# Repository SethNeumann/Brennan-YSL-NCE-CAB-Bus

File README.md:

# REPO NAME: Brennan-YSL-NCE-CAB-Bus
## License: Creative Commons Attribution-NonCommercial-ShareAlike

NCE Cab Bus Distribution board for the Yosemite Short Line Modular group, by Richard Brennan
- 4 RJ45 Jacks
- Optional power injection via 2.1mm barrel connector
- power LED

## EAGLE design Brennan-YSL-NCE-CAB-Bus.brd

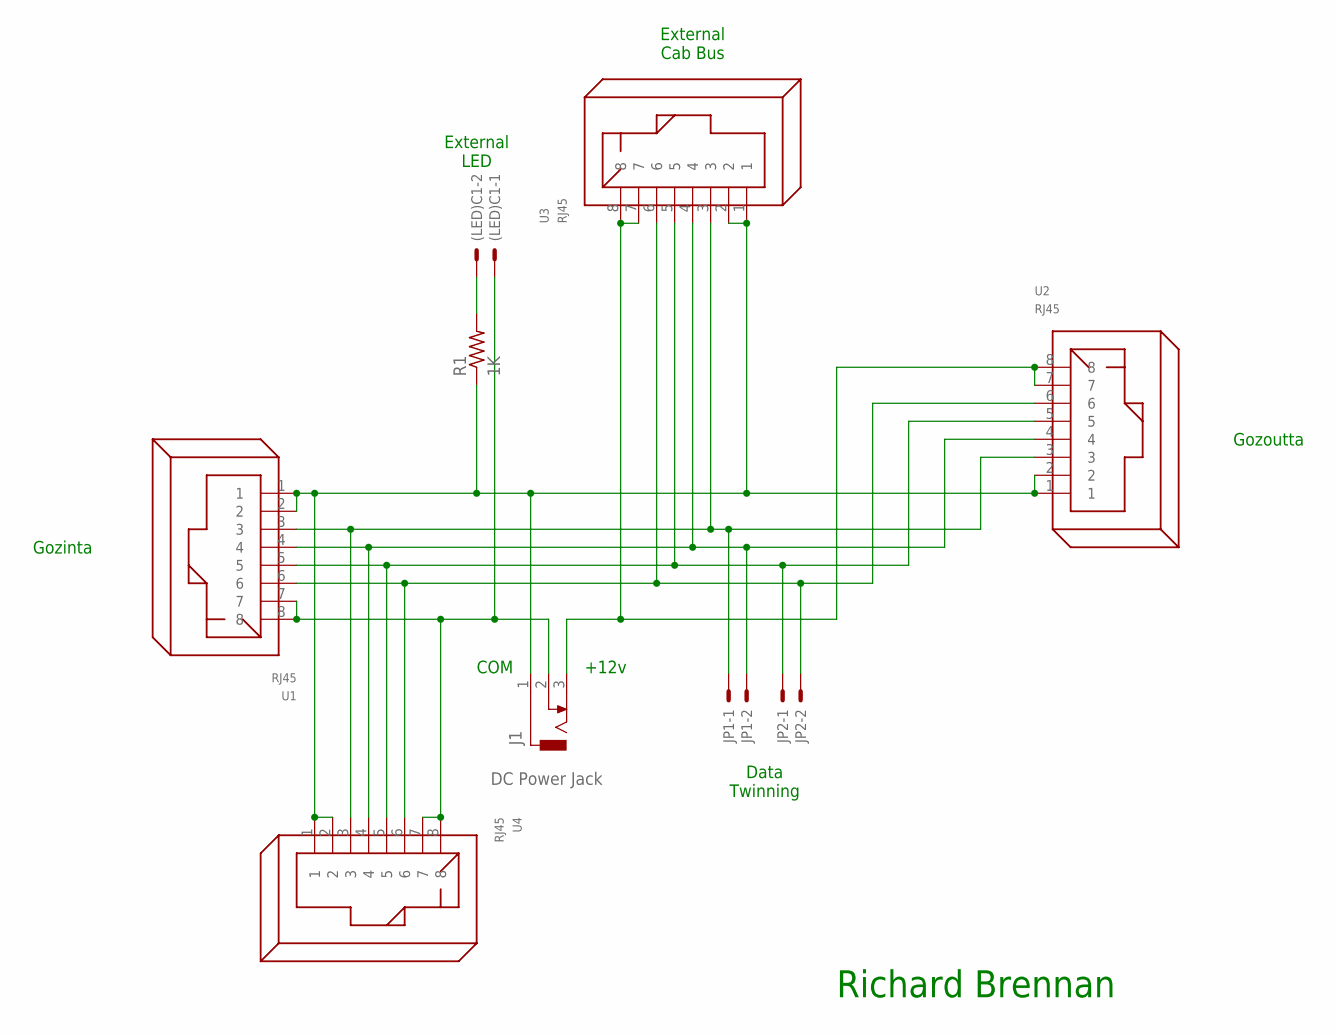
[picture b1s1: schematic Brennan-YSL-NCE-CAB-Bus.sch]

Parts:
(LED)C1: 22-23-2021
J1: DC Power Jack; DCJ0303
JP1, JP2: 22-23-2021
R1: 1K; 0207/10
U1, U2, U3, U4: RJ45

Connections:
+12V: J1.3, U2.7, U2.8, U3.7, U3.8
A2: JP1.1, U1.3, U2.3, U3.3, U4.3
B2: JP2.2, U1.6, U2.6, U3.6, U4.6
COM: J1.1, R1.1, U1.1, U1.2, U2.1, U2.2, U3.1, U3.2, U4.1, U4.2
DATA-A: JP1.2, U1.4, U2.4, U3.4, U4.4
DATA-B: JP2.1, U1.5, U2.5, U3.5, U4.5
unnamed: (LED)C1.2, R1.2
unnamed: (LED)C1.1, J1.2, U1.7, U1.8, U4.7, U4.8

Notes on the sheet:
External LED
Data Twinning
Gozinta
Gozoutta
External Cab Bus
+12v
COM
Richard Brennan

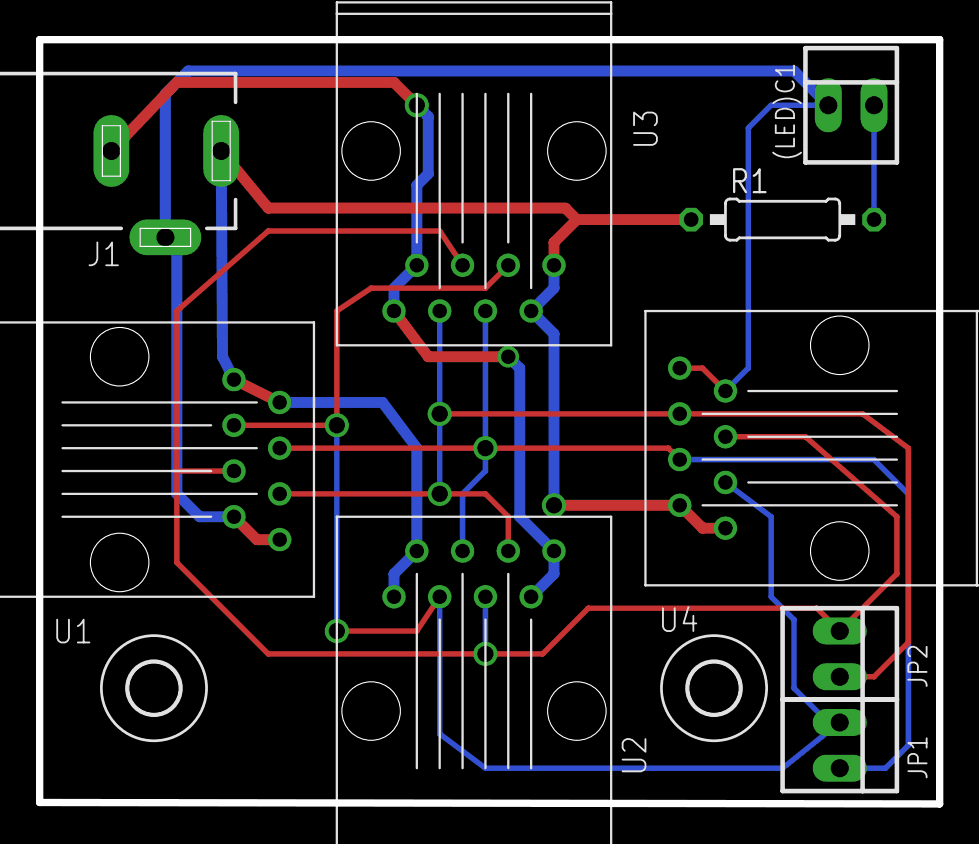
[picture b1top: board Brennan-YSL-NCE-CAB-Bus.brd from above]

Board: 2 copper layers, 50.0 x 42.5 mm, 12 parts (0 on the bottom side), 8 nets.

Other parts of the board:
U$1, U$2: 2,8
U$3: CA-PROP65WARNING

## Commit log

2021-08-13 intial commit
2021-08-13 initial commit
    all basic files
2021-08-14 minor changes to clean up
